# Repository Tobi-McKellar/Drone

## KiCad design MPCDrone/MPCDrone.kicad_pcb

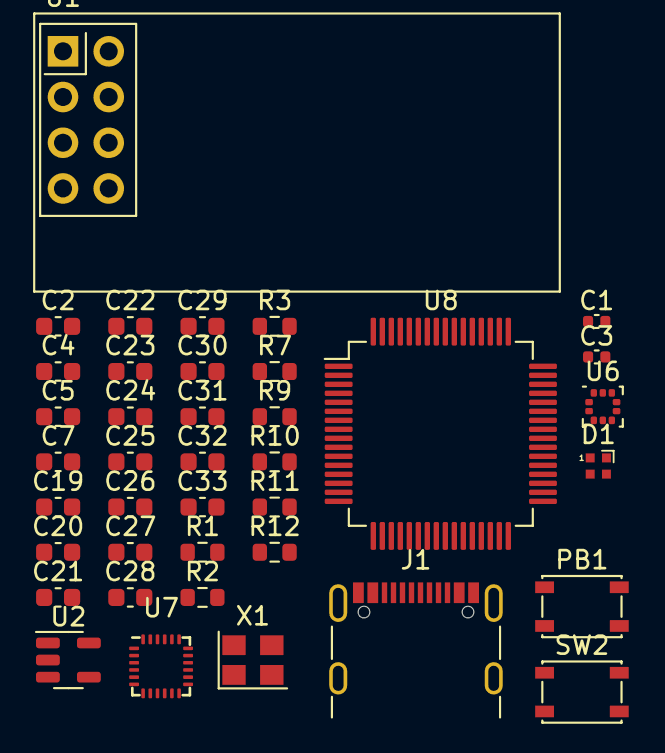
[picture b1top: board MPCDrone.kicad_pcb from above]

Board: 2 copper layers, 39 parts (0 on the bottom side), 27 nets, no tracks yet.

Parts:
C1, C3: 15p; C_0402_1005Metric
C2, C4, C28, C30: 1u; C_0603_1608Metric
C5: 10u; C_0603_1608Metric
C7: 4.7u; C_0603_1608Metric
C19: 2.2n; C_0603_1608Metric
C20, C22, C23, C24, C25, C26, C27, C31, C32, C33: 100n; C_0603_1608Metric
C21, C29: 10n; C_0603_1608Metric
D1: LED_RAGB; LED_SK6812_EC15_1.5x1.5mm
J1: USB_C_Receptacle_USB2.0; USB_C_Receptacle_GCT_USB4105-xx-A_16P_TopMnt_Horizontal
PB1: SW_Push; SW_SPST_PTS810
R1: 0; R_0603_1608Metric
R2, R3: 5k1; R_0603_1608Metric
R7, R10: 10k; R_0603_1608Metric
R9, R11, R12: 2k2; R_0603_1608Metric
SW2: SW_Push; SW_SPST_PTS810
U1: NRF24L01_Breakout; nRF24L01_Breakout
U2: LP2980IM5X-3.3; SOT-23-5
U6: LPS22HB; ST_HLGA-10_2x2mm_P0.5mm_LayoutBorder3x2y
U7: ICM-20948; InvenSense_QFN-24_3x3mm_P0.4mm
U8: STM32G431RBTx; LQFP-64_10x10mm_P0.5mm
X1: ABM8G-12.000MHZ-B4Y-T; Oscillator_SMD_Abracon_ASE-4Pin_3.2x2.5mm

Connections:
+3V3: C4.2, D1.2 (A), R7.1, R10.1, U2.5 (OUT), U7.8 (VDDIO), U7.13 (VDD)
+5V: C2.2, C5.1, J1.A4 (VBUS), J1.A9 (VBUS), J1.B4 (VBUS), J1.B9 (VBUS), U2.1 (IN), U2.3 (EN)
/MISO: U1.7 (MISO), U8.36 (PB14)
/MOSI: U1.6 (MOSI), U8.37 (PB15)
/NF_~CSN: U1.4 (~CSN), U8.33 (PB11)
/NRF_CE: U1.3 (CE), U8.34 (PB12)
/NRF_IRQ: U1.8 (IRQ), U8.30 (PB10)
/SCK: U1.5 (SCK), U8.35 (PB13)
/SCL: U6.2 (SCL), U7.23 (SCL/SCLK), U8.49 (PA13)
/SDA: U6.4 (SDA), U7.24 (SDA/SDI), U8.50 (PA14)
/USB_N: J1.A7 (D-), J1.B7 (D-)
/USB_P: J1.A6 (D+), J1.B6 (D+)
/XIN: C3.2, U8.5 (PF0), X1.3
/XOUT: C1.2, U8.6 (PF1), X1.1
GND: C1.1, C2.1, C3.1, C4.1, C5.2, C7.2, C19.2, C20.2, C21.1, C22.2, C23.2, C24.2, C25.2, C26.2, C27.2, C28.2, C29.2, C30.2, C31.2, C32.2, C33.1, J1.A1 (GND), J1.A12 (GND), J1.B1 (GND), J1.B12 (GND), PB1.1, R1.2, R2.2, R3.2, SW2.1, U1.1 (GND), U2.2 (GND), U6.3 (RES), U6.5 (SA0), U6.8 (GND), U6.9 (GND), U7.9 (SDO/AD0), U7.18 (GND), U7.20 (GND), U8.15 (VSS), U8.27 (VSSA), U8.31 (VSS), U8.47 (VSS), U8.63 (VSS), X1.2, X1.4
unnamed: D1.4 (BK), R9.1
unnamed: D1.3 (GK), R11.1
unnamed: D1.1 (RK), R12.1
unnamed: J1.A5 (CC1), R2.1
unnamed: J1.B5 (CC2), R3.1
unnamed: J1.S1 (SHIELD), R1.1
unnamed: PB1.2, R10.2
unnamed: R7.2, SW2.2
unnamed: C32.1, U6.10 (VDD)
unnamed: C33.2, U7.10 (REGOUT)
VDD: C7.1, C23.1, C24.1, C25.1, C26.1, C27.1, U1.2 (VCC), U6.1 (Vdd_IO), U6.6 (~CS), U8.16 (VDD), U8.32 (VDD), U8.48 (VDD), U8.64 (VDD)
VDDA: C28.1, C29.1, C30.1, C31.1, U8.28 (VREF+), U8.29 (VDDA)

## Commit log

2024-07-08 Add STMCubeIDE stuff to gitignore.
2024-07-08 Initial hardware for the drone. Only a basic schematic with missing features for now.
2024-07-08 Add more STM32CubeIDE files to gitignore.
2024-07-08 More STM32 to gitignore.
2024-07-08 initialising pins on stm32.
